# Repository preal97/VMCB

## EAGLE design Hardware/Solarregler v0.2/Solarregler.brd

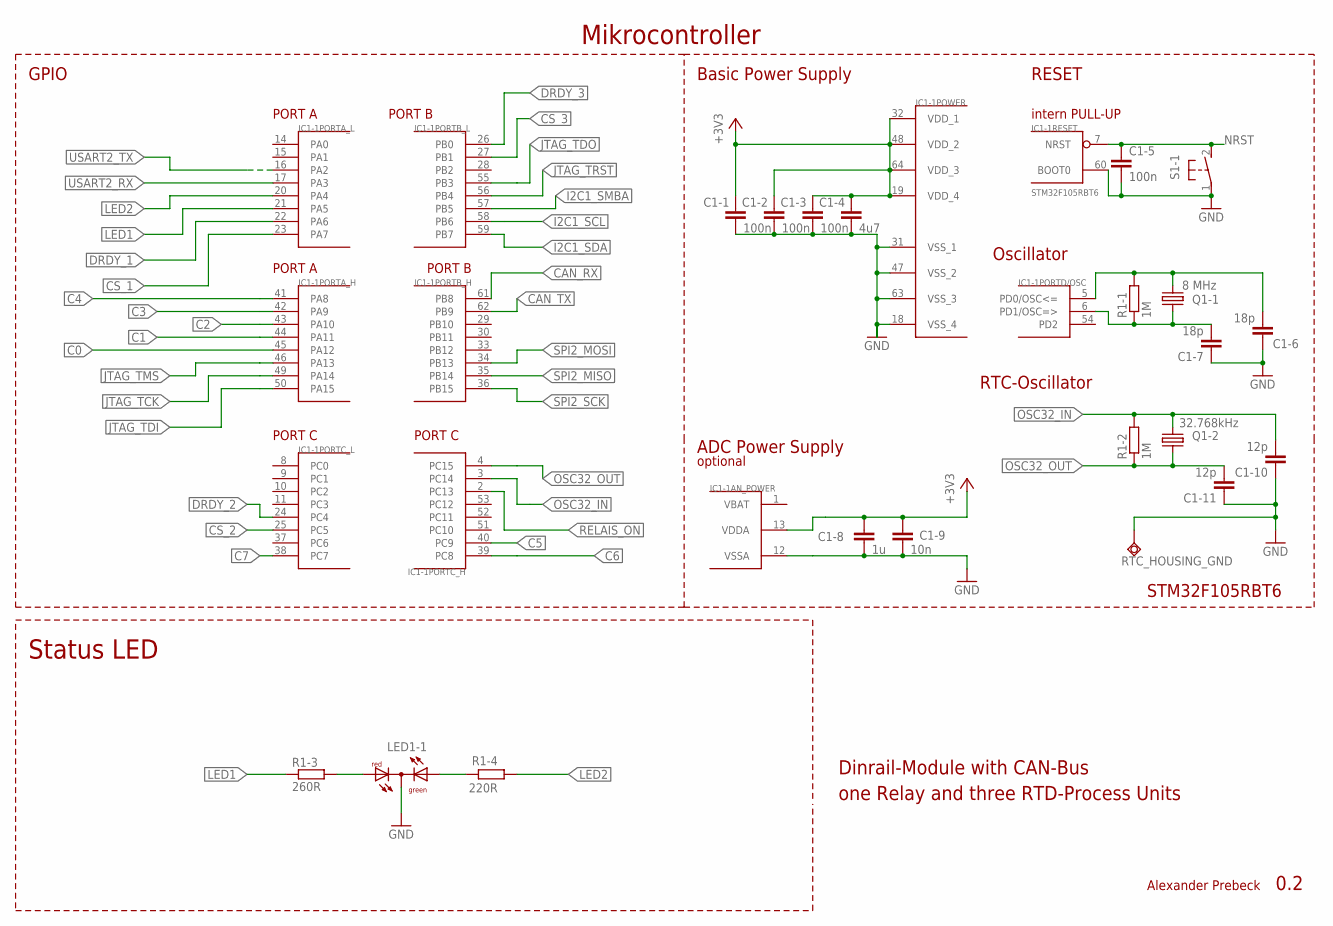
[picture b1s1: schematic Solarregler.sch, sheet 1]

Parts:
C1-1, C1-2, C1-3, C1-5: 100n; C0603; MPN C0805C104K1RAC AUTO
C1-4: 4u7; C1206; MPN GRM21BR61A475KA73L
C1-6, C1-7: 18p; C0603; MPN C0805C270J5GACTU
C1-8: 1u; C0805; MPN GRM21BR71E105KA99L
C1-9: 10n; C0603; MPN MC0805B103K500CT
C1-10, C1-11: 12p; C0603; MPN C0805C270J5GACTU
IC1-1: STM32F105RBT6; TQFP64
LED1-1: DUOLED-RG-C; DUOLED-C-5MM
Q1-1: 8 MHz; SMD_QUARZ_6X3.5MM
Q1-2: 32.768kHz; THROUGH_HOLE_QUARZ_RTC
R1-1, R1-2: 1M; R0603
R1-3: 260R; R0603
R1-4: 220R; R0603
RTC_HOUSING_GND: TPSQTP20SQ; TP20SQ
S1-1: 31-XX; B3F-31XX

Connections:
+3V3: C1-1.1, C1-2.1, C1-3.1, C1-4.1, C1-8.1, C1-9.1, IC1-1.13 (VDDA), IC1-1.19 (VDD_4), IC1-1.32 (VDD_1), IC1-1.48 (VDD_2), IC1-1.64 (VDD_3); also elsewhere on the board
C0: IC1-1.45 (PA12); also elsewhere on the board
C1: IC1-1.44 (PA11); also elsewhere on the board
C2: IC1-1.43 (PA10); also elsewhere on the board
C3: IC1-1.42 (PA9); also elsewhere on the board
C4: IC1-1.41 (PA8); also elsewhere on the board
C5: IC1-1.40 (PC9); also elsewhere on the board
C6: IC1-1.39 (PC8); also elsewhere on the board
C7: IC1-1.38 (PC7); also elsewhere on the board
CAN_RX: IC1-1.61 (PB8); also elsewhere on the board
CAN_TX: IC1-1.62 (PB9); also elsewhere on the board
CS_1: IC1-1.23 (PA7); also elsewhere on the board
CS_2: IC1-1.25 (PC5); also elsewhere on the board
CS_3: IC1-1.27 (PB1); also elsewhere on the board
DRDY_1: IC1-1.22 (PA6); also elsewhere on the board
DRDY_2: IC1-1.24 (PC4); also elsewhere on the board
DRDY_3: IC1-1.26 (PB0); also elsewhere on the board
GND: C1-1.2, C1-2.2, C1-3.2, C1-4.2, C1-5.2, C1-6.1, C1-7.1, C1-8.2, C1-9.2, C1-10.1, C1-11.1, IC1-1.12 (VSSA), IC1-1.18 (VSS_4), IC1-1.31 (VSS_1), IC1-1.47 (VSS_2), IC1-1.60 (BOOT0), IC1-1.63 (VSS_3), LED1-1.C, RTC_HOUSING_GND.TP, S1-1.1; also elsewhere on the board
I2C1_SCL: IC1-1.58 (PB6); also elsewhere on the board
I2C1_SDA: IC1-1.59 (PB7); also elsewhere on the board
I2C1_SMBA: IC1-1.57 (PB5); also elsewhere on the board
JTAG_TCK: IC1-1.49 (PA14); also elsewhere on the board
JTAG_TDI: IC1-1.50 (PA15); also elsewhere on the board
JTAG_TDO: IC1-1.55 (PB3); also elsewhere on the board
JTAG_TMS: IC1-1.46 (PA13); also elsewhere on the board
JTAG_TRST: IC1-1.56 (PB4); also elsewhere on the board
LED1: IC1-1.21 (PA5), R1-3.1
LED2: IC1-1.20 (PA4), R1-4.1
unnamed: LED1-1.AX (AG), R1-4.2
unnamed: LED1-1.AR, R1-3.2
unnamed: C1-7.2, IC1-1.6 (PD1/OSC=>), Q1-1.1, R1-1.1
unnamed: C1-6.2, IC1-1.5 (PD0/OSC<=), Q1-1.2, R1-1.2
NRST: C1-5.1, IC1-1.7 (NRST), S1-1.2 (S); also elsewhere on the board
OSC32_IN: C1-10.2, IC1-1.3 (PC14), Q1-2.P$1 (1), R1-2.2
OSC32_OUT: C1-11.2, IC1-1.4 (PC15), Q1-2.P$2 (2), R1-2.1
RELAIS_ON: IC1-1.2 (PC13); also elsewhere on the board
SPI2_MISO: IC1-1.35 (PB14); also elsewhere on the board
SPI2_MOSI: IC1-1.34 (PB13); also elsewhere on the board
SPI2_SCK: IC1-1.36 (PB15); also elsewhere on the board
USART2_RX: IC1-1.17 (PA3); also elsewhere on the board
USART2_TX: IC1-1.16 (PA2); also elsewhere on the board
VBAT: IC1-1.1 (VBAT)

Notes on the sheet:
Mikrocontroller
Dinrail-Module with CAN-Bus
one Relay and three RTD-Process Units
0.2
Status LED
Alexander Prebeck
intern PULL-UP
RESET
PORT A
PORT B
PORT C
GPIO
Oscillator
ADC Power Supply
Basic Power Supply
STM32F105RBT6
RTC-Oscillator
optional

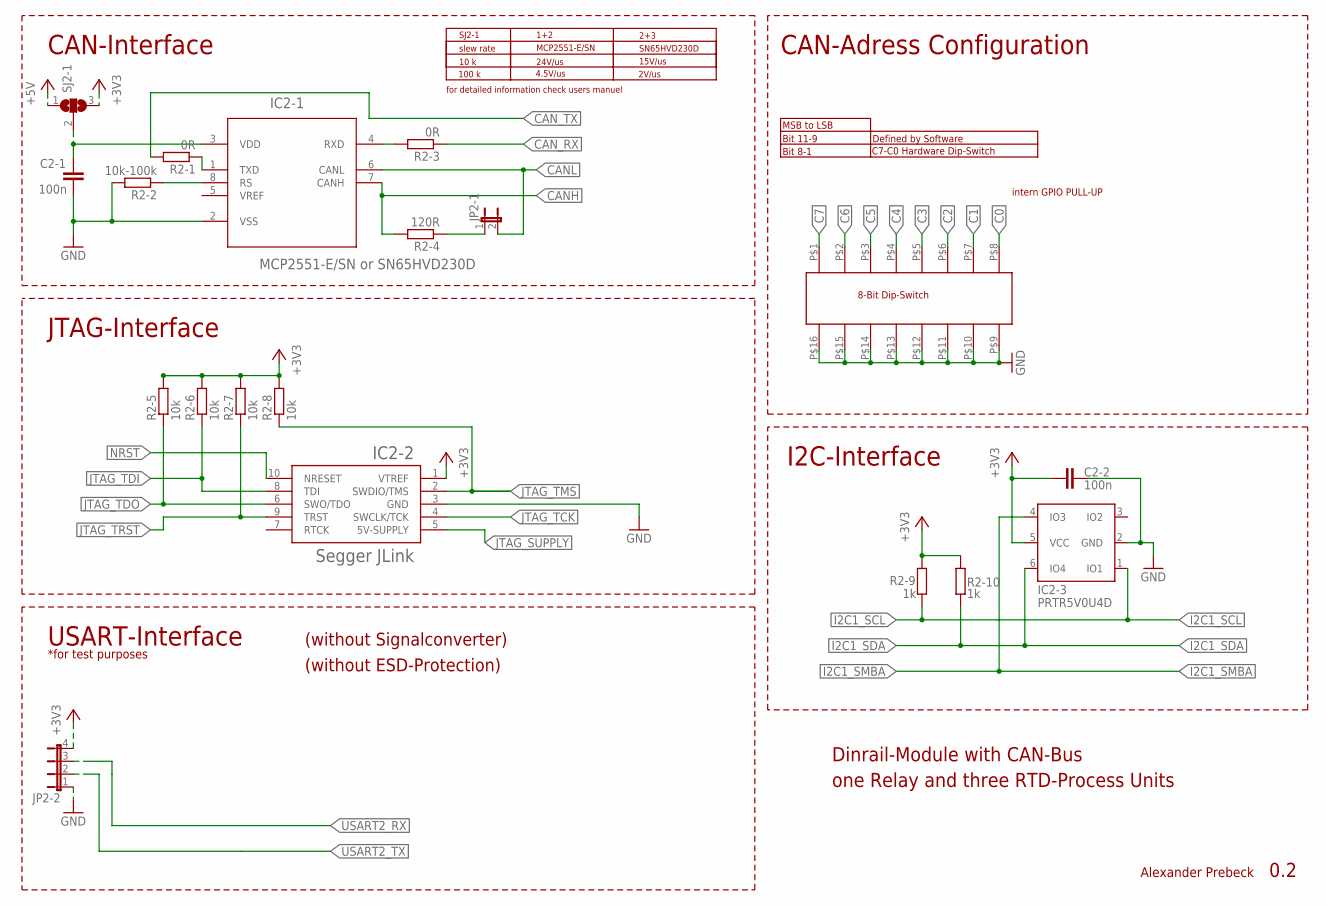
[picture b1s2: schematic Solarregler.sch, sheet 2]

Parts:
C2-1, C2-2: 100n; C0603; MPN C0805C104K1RAC AUTO
DIP21: MULTICOMP
IC2-1: MCP2551-E/SN or SN65HVD230D; SOIC127P600X175-8N
IC2-2: J-LINK-10PIN-HOLES
IC2-3: PRTR5V0U4D; SC74; MPN PRTR5V0U4D,125.
JP2-1: JP1E; JP1
JP2-2: JP4E; JP4
R2-1, R2-3: 0R; R0603
R2-2: 10k-100k; R0603
R2-4: 120R; R0603
R2-5, R2-6, R2-7, R2-8: 10k; R0603
R2-9, R2-10: 1k; R0603
SJ2-1: SJ2W; SJ_2

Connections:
+3V3: C2-2.1, IC2-2.1 (VTREF), IC2-3.5 (VCC), JP2-2.4, R2-5.2, R2-6.2, R2-7.2, R2-8.2, R2-9.2, R2-10.2, SJ2-1.3; also elsewhere on the board
+5V: SJ2-1.1; also elsewhere on the board
C0: DIP21.P$8; also elsewhere on the board
C1: DIP21.P$7; also elsewhere on the board
C2: DIP21.P$6; also elsewhere on the board
C3: DIP21.P$5; also elsewhere on the board
C4: DIP21.P$4; also elsewhere on the board
C5: DIP21.P$3; also elsewhere on the board
C6: DIP21.P$2; also elsewhere on the board
C7: DIP21.P$1 (1); also elsewhere on the board
CANH: IC2-1.7 (CANH), R2-4.2; also elsewhere on the board
CANL: IC2-1.6 (CANL), JP2-1.2; also elsewhere on the board
CAN_RX: R2-3.1; also elsewhere on the board
CAN_TERM2: JP2-1.1, R2-4.1
CAN_TX: R2-1.2; also elsewhere on the board
GND: C2-1.2, C2-2.2, DIP21.P$9, DIP21.P$10, DIP21.P$11, DIP21.P$12, DIP21.P$13, DIP21.P$14, DIP21.P$15, DIP21.P$16, IC2-1.2 (VSS), IC2-2.3 (GND), IC2-3.2 (GND), JP2-2.1, R2-2.2; also elsewhere on the board
I2C1_SCL: IC2-3.1 (IO1), R2-9.1; also elsewhere on the board
I2C1_SDA: IC2-3.6 (IO4), R2-10.1; also elsewhere on the board
I2C1_SMBA: IC2-3.4 (IO3); also elsewhere on the board
JTAG_SUPPLY: IC2-2.5 (5V-SUPPLY); also elsewhere on the board
JTAG_TCK: IC2-2.4 (SWCLK/TCK); also elsewhere on the board
JTAG_TDI: IC2-2.8 (TDI), R2-6.1; also elsewhere on the board
JTAG_TDO: IC2-2.6 (SWO/TDO), R2-5.1; also elsewhere on the board
JTAG_TMS: IC2-2.2 (SWDIO/TMS), R2-8.1; also elsewhere on the board
JTAG_TRST: IC2-2.9 (TRST), R2-7.1; also elsewhere on the board
unnamed: IC2-1.4 (RXD), R2-3.2
unnamed: IC2-1.1 (TXD), R2-1.1
unnamed: IC2-1.8 (RS), R2-2.1
unnamed: C2-1.1, IC2-1.3 (VDD), SJ2-1.2
NRST: IC2-2.10 (NRESET); also elsewhere on the board
USART2_RX: JP2-2.3; also elsewhere on the board
USART2_TX: JP2-2.2; also elsewhere on the board

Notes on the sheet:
CAN-Interface
I2C-Interface
JTAG-Interface
USART-Interface
Dinrail-Module with CAN-Bus
0.2
one Relay and three RTD-Process Units
Alexander Prebeck
*for test purposes
slew rate
MCP2551-E/SN
SN65HVD230D
10 k
100 k
24V/us
4.5V/us
15V/us
2V/us
for detailed information check users manuel
SJ2-1
1+2
2+3
CAN-Adress Configuration
Bit 8-1
Bit 11-9
C7-C0 Hardware Dip-Switch
Defined by Software
MSB to LSB
intern GPIO PULL-UP
8-Bit Dip-Switch
(without Signalconverter)
(without ESD-Protection)

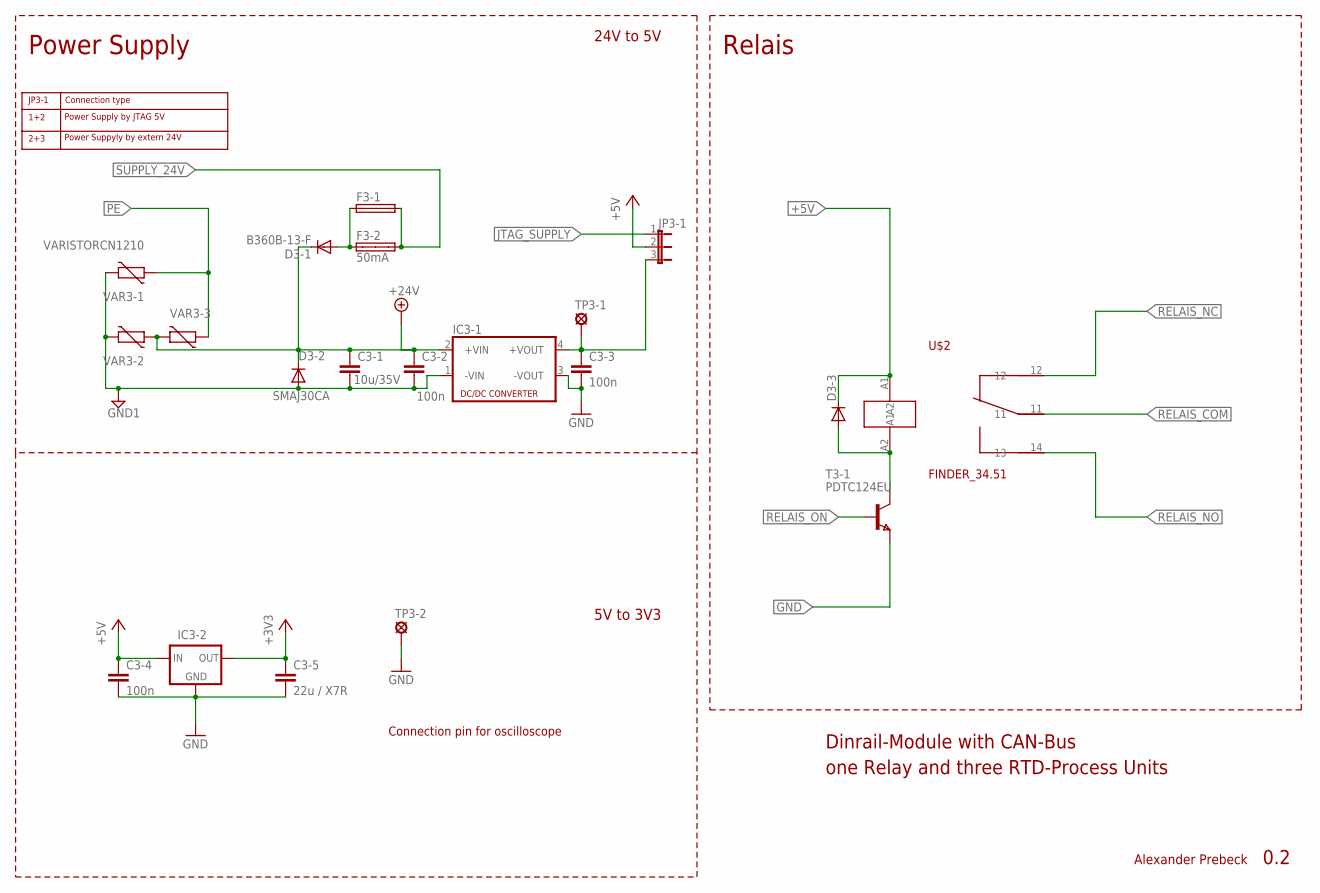
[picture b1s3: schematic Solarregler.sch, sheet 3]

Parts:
C3-1: 10u/35V; C0805; MPN GRM31CC8YA106KA12L
C3-2, C3-3, C3-4: 100n; C0603; MPN C0805C104K1RAC AUTO
C3-5: 22u / X7R; C0805; MPN C0805C104K1RAC AUTO
D3-1: B360B-13-F; SMB; MPN B360B-13-F
D3-2: SMAJ30CA; DO214AA; MPN SMAJ30CA
D3-3: DIODE-SMB; SMB
F3-1: FUSE_1210; 1210
F3-2: 50mA; SHK20Q; MPN 0031.8201
IC3-1: SIM1; 4SIL; MPN IE2405S
IC3-2: MIC5209; SOT223; MPN MIC5209-3.3YS TR
JP3-1: JP2E; JP2
T3-1: PDTC124EU; SOT323
TP3-1, TP3-2: LSP10
U$2: FINDER_34.51; SERIES_34
VAR3-1, VAR3-2, VAR3-3: VARISTORCN1210; CT/CN1210; MPN VC121030H620DP

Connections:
+3V3: C3-5.1, IC3-2.3 (OUT); also elsewhere on the board
+5V: C3-4.1, D3-3.C, IC3-2.1 (IN), JP3-1.2, U$2.A1; also elsewhere on the board
+24V: C3-1.1, C3-2.1, D3-1.C, D3-2.C, IC3-1.2 (+VIN), VAR3-2.2, VAR3-3.2
GND: C3-3.2, C3-4.2, C3-5.2, IC3-1.3 (-VOUT), IC3-2.2 (GND), IC3-2.4 (GND), T3-1.3 (E), TP3-2.MP; also elsewhere on the board
GND1: C3-1.2, C3-2.2, D3-2.A, IC3-1.1 (-VIN), VAR3-1.1, VAR3-2.1; also elsewhere on the board
JTAG_SUPPLY: JP3-1.1; also elsewhere on the board
unnamed: D3-3.A, T3-1.1 (C), U$2.A2
unnamed: C3-3.1, IC3-1.4 (+VOUT), JP3-1.3, TP3-1.MP
unnamed: D3-1.A, F3-1.1, F3-2.1A
PE: VAR3-1.2, VAR3-3.1; also elsewhere on the board
RELAIS_COM: U$2.11; also elsewhere on the board
RELAIS_NC: U$2.12; also elsewhere on the board
RELAIS_NO: U$2.14 (13); also elsewhere on the board
RELAIS_ON: T3-1.2 (B); also elsewhere on the board
SUPPLY_24V: F3-1.2, F3-2.2A; also elsewhere on the board

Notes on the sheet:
Power Supply
Connection pin for oscilloscope
24V to 5V
5V to 3V3
JP3-1
1+2
2+3
Power Supply by JTAG 5V
Power Suppyly by extern 24V
Connection type
Relais
0.2
Dinrail-Module with CAN-Bus
one Relay and three RTD-Process Units
Alexander Prebeck

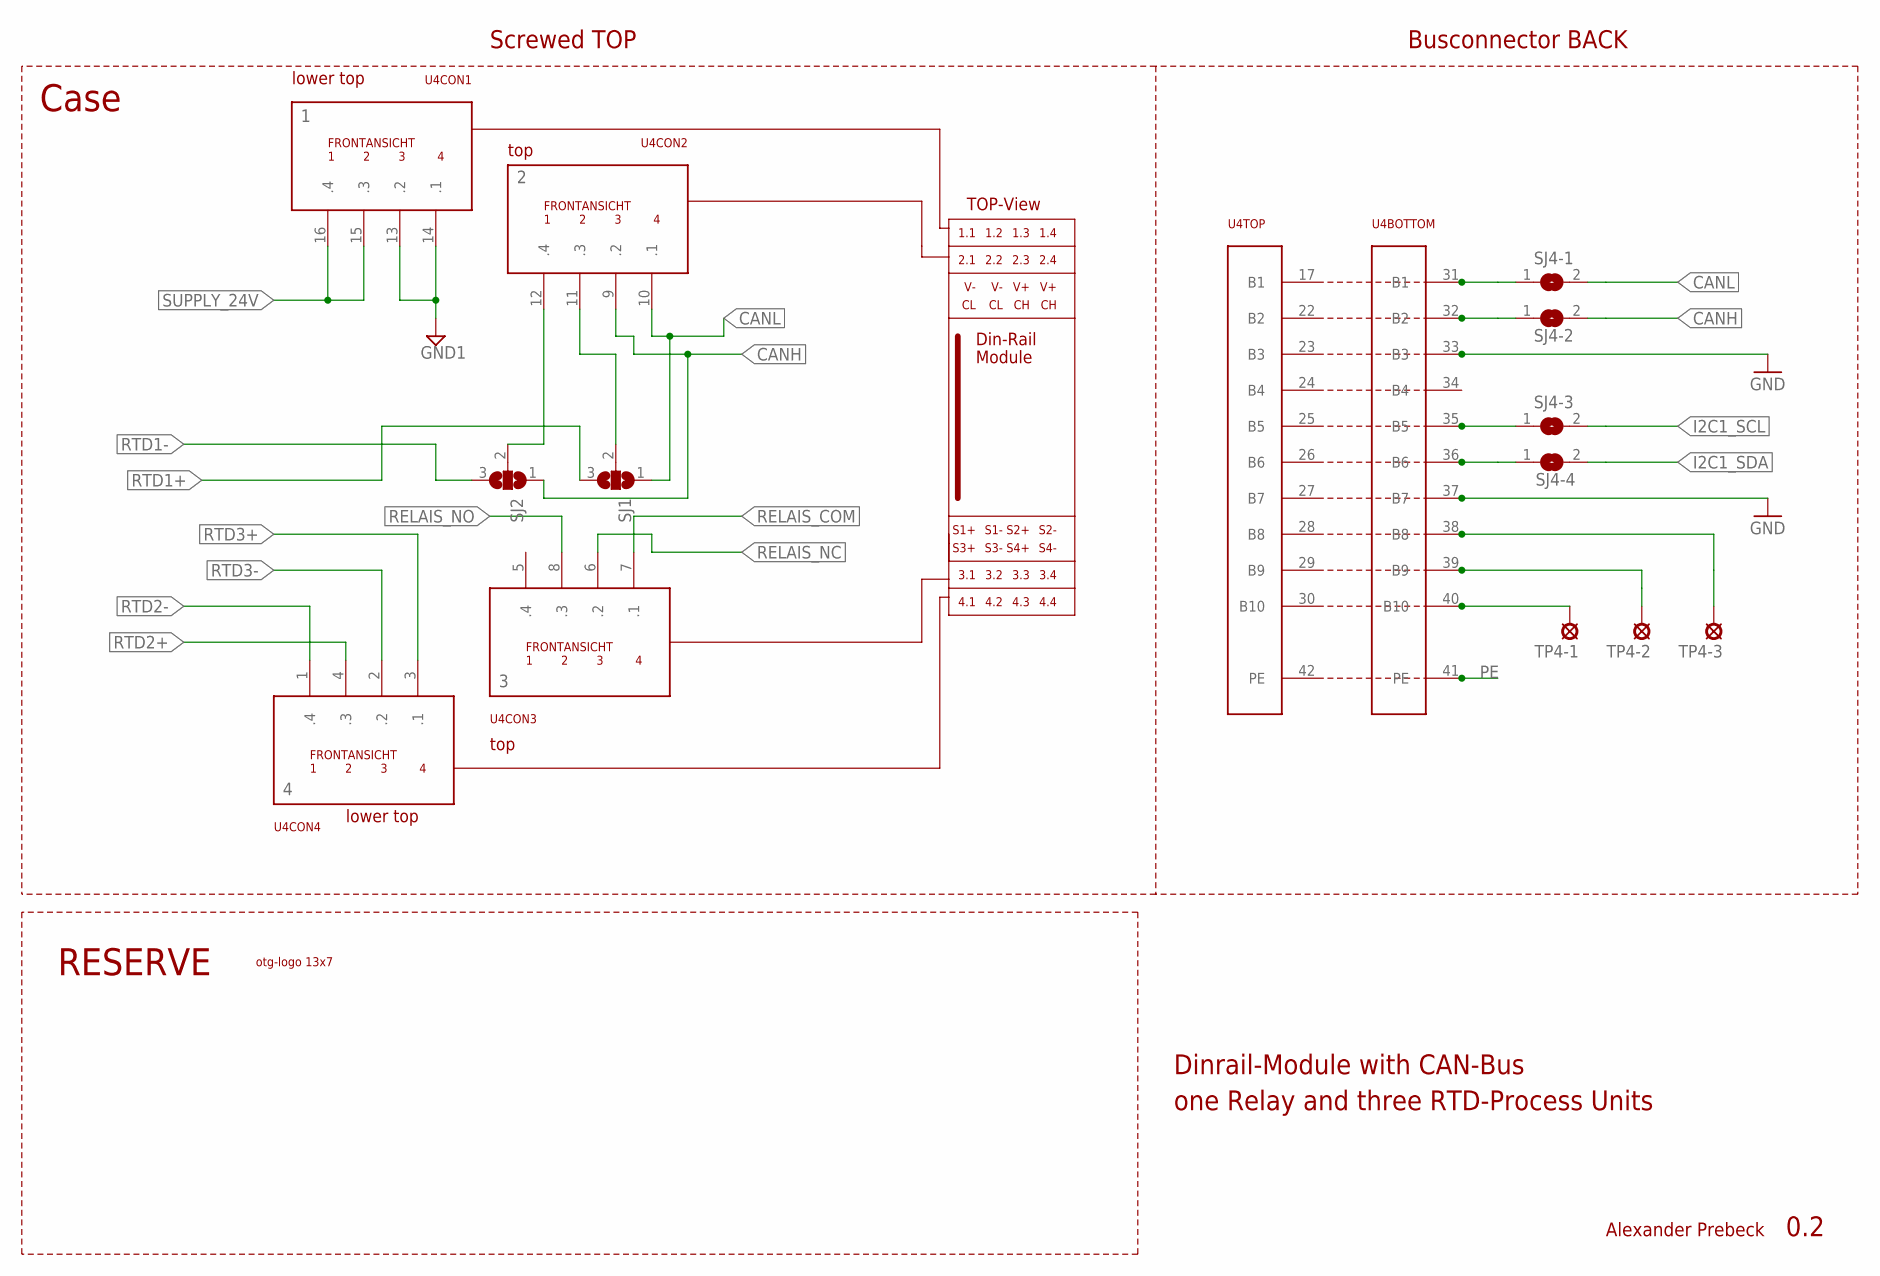
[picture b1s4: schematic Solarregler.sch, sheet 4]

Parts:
SJ1, SJ2: SJ2W; SJ_2
SJ4-1, SJ4-2, SJ4-3, SJ4-4: SJW
TP4-1, TP4-2, TP4-3: LSP10
U4: HUTSCHIENE_DEV; HUTSCHIENE
U$1: OTH-LOGO13X7; OTH-LOGO_SMALL

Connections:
CANH: SJ2.1, SJ4-2.2, U4.9 (.2); also elsewhere on the board
CANL: SJ1.1, SJ4-1.2, U4.10 (.1); also elsewhere on the board
GND: U4.33 (B3), U4.37 (B7); also elsewhere on the board
GND1: U4.13 (.2), U4.14 (.1); also elsewhere on the board
I2C1_SCL: SJ4-3.2; also elsewhere on the board
I2C1_SDA: SJ4-4.2; also elsewhere on the board
unnamed: SJ1.2, U4.11 (.3)
unnamed: SJ2.2, U4.12 (.4)
unnamed: SJ4-1.1, U4.31 (B1)
unnamed: SJ4-2.1, U4.32 (B2)
unnamed: SJ4-3.1, U4.35 (B5)
unnamed: SJ4-4.1, U4.36 (B6)
unnamed: TP4-3.MP, U4.38 (B8)
unnamed: TP4-2.MP, U4.39 (B9)
unnamed: TP4-1.MP, U4.40 (B10)
PE: U4.41 (PE); also elsewhere on the board
RELAIS_COM: U4.7 (.1); also elsewhere on the board
RELAIS_NC: U4.6 (.2); also elsewhere on the board
RELAIS_NO: U4.8 (.3); also elsewhere on the board
RTD1+: SJ1.3; also elsewhere on the board
RTD1-: SJ2.3; also elsewhere on the board
RTD2+: U4.4 (.3); also elsewhere on the board
RTD2-: U4.1 (.4); also elsewhere on the board
RTD3+: U4.3 (.1); also elsewhere on the board
RTD3-: U4.2 (.2); also elsewhere on the board
SUPPLY_24V: U4.15 (.3), U4.16 (.4); also elsewhere on the board

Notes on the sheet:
Case
lower top
top
Screwed TOP
Busconnector BACK
1.1
1.2
1.3
1.4
2.1
2.2
2.3
2.4
TOP-View
Din-Rail
Module
Dinrail-Module with CAN-Bus
0.2
one Relay and three RTD-Process Units
Alexander Prebeck
3.1
3.2
3.3
3.4
4.1
4.2
4.3
4.4
S1-
S1+
S3+
S2-
S2+
S4+
S4-
S3-
RESERVE

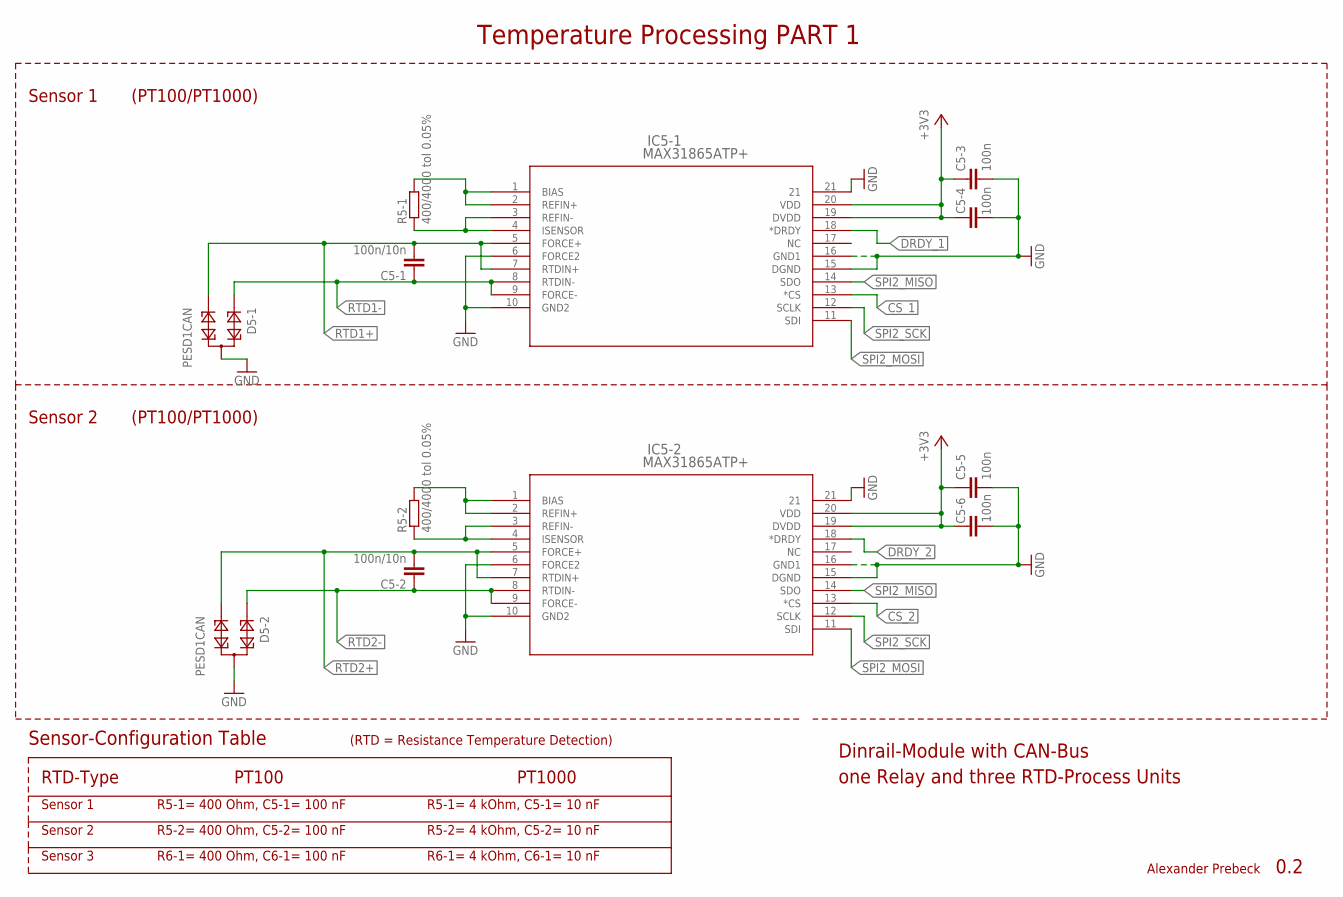
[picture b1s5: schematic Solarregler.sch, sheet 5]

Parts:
C5-1, C5-2: 100n/10n; C0603
C5-3, C5-4, C5-5, C5-6: 100n; C0603
D5-1, D5-2: PESD1CAN; SOT23
IC5-1, IC5-2: MAX31865ATP+; 21-0140L_T2055-5
R5-1, R5-2: 400/4000 tol 0.05%; R0603

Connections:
+3V3: C5-3.1, C5-4.1, C5-5.1, C5-6.1, IC5-1.19 (DVDD), IC5-1.20 (VDD), IC5-2.19 (DVDD), IC5-2.20 (VDD); also elsewhere on the board
CS_1: IC5-1.13 (*CS); also elsewhere on the board
CS_2: IC5-2.13 (*CS); also elsewhere on the board
DRDY_1: IC5-1.18 (*DRDY); also elsewhere on the board
DRDY_2: IC5-2.18 (*DRDY); also elsewhere on the board
GND: C5-3.2, C5-4.2, C5-5.2, C5-6.2, D5-1.3, D5-2.3, IC5-1.6 (FORCE2), IC5-1.10 (GND2), IC5-1.15 (DGND), IC5-1.16 (GND1), IC5-1.21, IC5-2.6 (FORCE2), IC5-2.10 (GND2), IC5-2.15 (DGND), IC5-2.16 (GND1), IC5-2.21; also elsewhere on the board
unnamed: IC5-1.1 (BIAS), IC5-1.2 (REFIN+), R5-1.2
unnamed: IC5-1.3 (REFIN-), IC5-1.4 (ISENSOR), R5-1.1
unnamed: IC5-2.1 (BIAS), IC5-2.2 (REFIN+), R5-2.2
unnamed: IC5-2.3 (REFIN-), IC5-2.4 (ISENSOR), R5-2.1
RTD1+: C5-1.2, D5-1.2, IC5-1.5 (FORCE+), IC5-1.7 (RTDIN+); also elsewhere on the board
RTD1-: C5-1.1, D5-1.1, IC5-1.8 (RTDIN-), IC5-1.9 (FORCE-); also elsewhere on the board
RTD2+: C5-2.2, D5-2.2, IC5-2.5 (FORCE+), IC5-2.7 (RTDIN+); also elsewhere on the board
RTD2-: C5-2.1, D5-2.1, IC5-2.8 (RTDIN-), IC5-2.9 (FORCE-); also elsewhere on the board
SPI2_MISO: IC5-1.14 (SDO), IC5-2.14 (SDO); also elsewhere on the board
SPI2_MOSI: IC5-1.11 (SDI), IC5-2.11 (SDI); also elsewhere on the board
SPI2_SCK: IC5-1.12 (SCLK), IC5-2.12 (SCLK); also elsewhere on the board

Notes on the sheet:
Temperature Processing PART 1
Sensor 1
Sensor 2
Dinrail-Module with CAN-Bus
0.2
one Relay and three RTD-Process Units
Alexander Prebeck
Sensor-Configuration Table
(PT100/PT1000)
(RTD = Resistance Temperature Detection)
PT100
PT1000
Sensor 3
R5-1= 400 Ohm, C5-1= 100 nF
R5-2= 400 Ohm, C5-2= 100 nF
R6-1= 400 Ohm, C6-1= 100 nF
R5-1= 4 kOhm, C5-1= 10 nF
R5-2= 4 kOhm, C5-2= 10 nF
R6-1= 4 kOhm, C6-1= 10 nF
RTD-Type

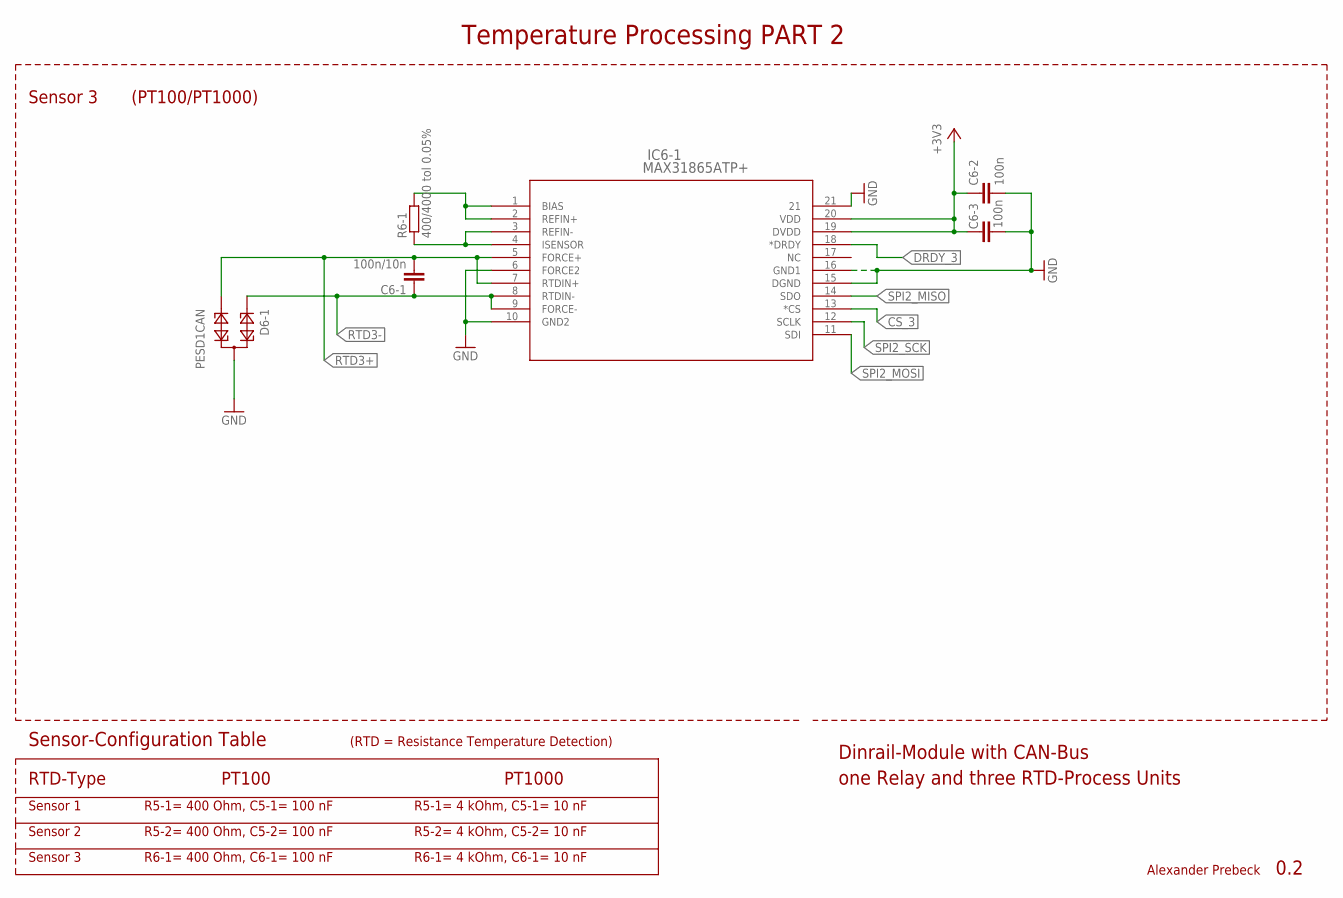
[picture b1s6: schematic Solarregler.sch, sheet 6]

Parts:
C6-1: 100n/10n; C0603
C6-2, C6-3: 100n; C0603
D6-1: PESD1CAN; SOT23
IC6-1: MAX31865ATP+; 21-0140L_T2055-5
R6-1: 400/4000 tol 0.05%; R0603

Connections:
+3V3: C6-2.1, C6-3.1, IC6-1.19 (DVDD), IC6-1.20 (VDD); also elsewhere on the board
CS_3: IC6-1.13 (*CS); also elsewhere on the board
DRDY_3: IC6-1.18 (*DRDY); also elsewhere on the board
GND: C6-2.2, C6-3.2, D6-1.3, IC6-1.6 (FORCE2), IC6-1.10 (GND2), IC6-1.15 (DGND), IC6-1.16 (GND1), IC6-1.21; also elsewhere on the board
unnamed: IC6-1.1 (BIAS), IC6-1.2 (REFIN+), R6-1.2
unnamed: IC6-1.3 (REFIN-), IC6-1.4 (ISENSOR), R6-1.1
RTD3+: C6-1.2, D6-1.2, IC6-1.5 (FORCE+), IC6-1.7 (RTDIN+); also elsewhere on the board
RTD3-: C6-1.1, D6-1.1, IC6-1.8 (RTDIN-), IC6-1.9 (FORCE-); also elsewhere on the board
SPI2_MISO: IC6-1.14 (SDO); also elsewhere on the board
SPI2_MOSI: IC6-1.11 (SDI); also elsewhere on the board
SPI2_SCK: IC6-1.12 (SCLK); also elsewhere on the board

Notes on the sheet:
Dinrail-Module with CAN-Bus
0.2
one Relay and three RTD-Process Units
Alexander Prebeck
Temperature Processing PART 2
Sensor 3
(PT100/PT1000)
Sensor-Configuration Table
Sensor 1
PT100
PT1000
Sensor 2
R5-1= 400 Ohm, C5-1= 100 nF
R5-2= 400 Ohm, C5-2= 100 nF
R6-1= 400 Ohm, C6-1= 100 nF
R5-1= 4 kOhm, C5-1= 10 nF
R5-2= 4 kOhm, C5-2= 10 nF
R6-1= 4 kOhm, C6-1= 10 nF
RTD-Type
(RTD = Resistance Temperature Detection)

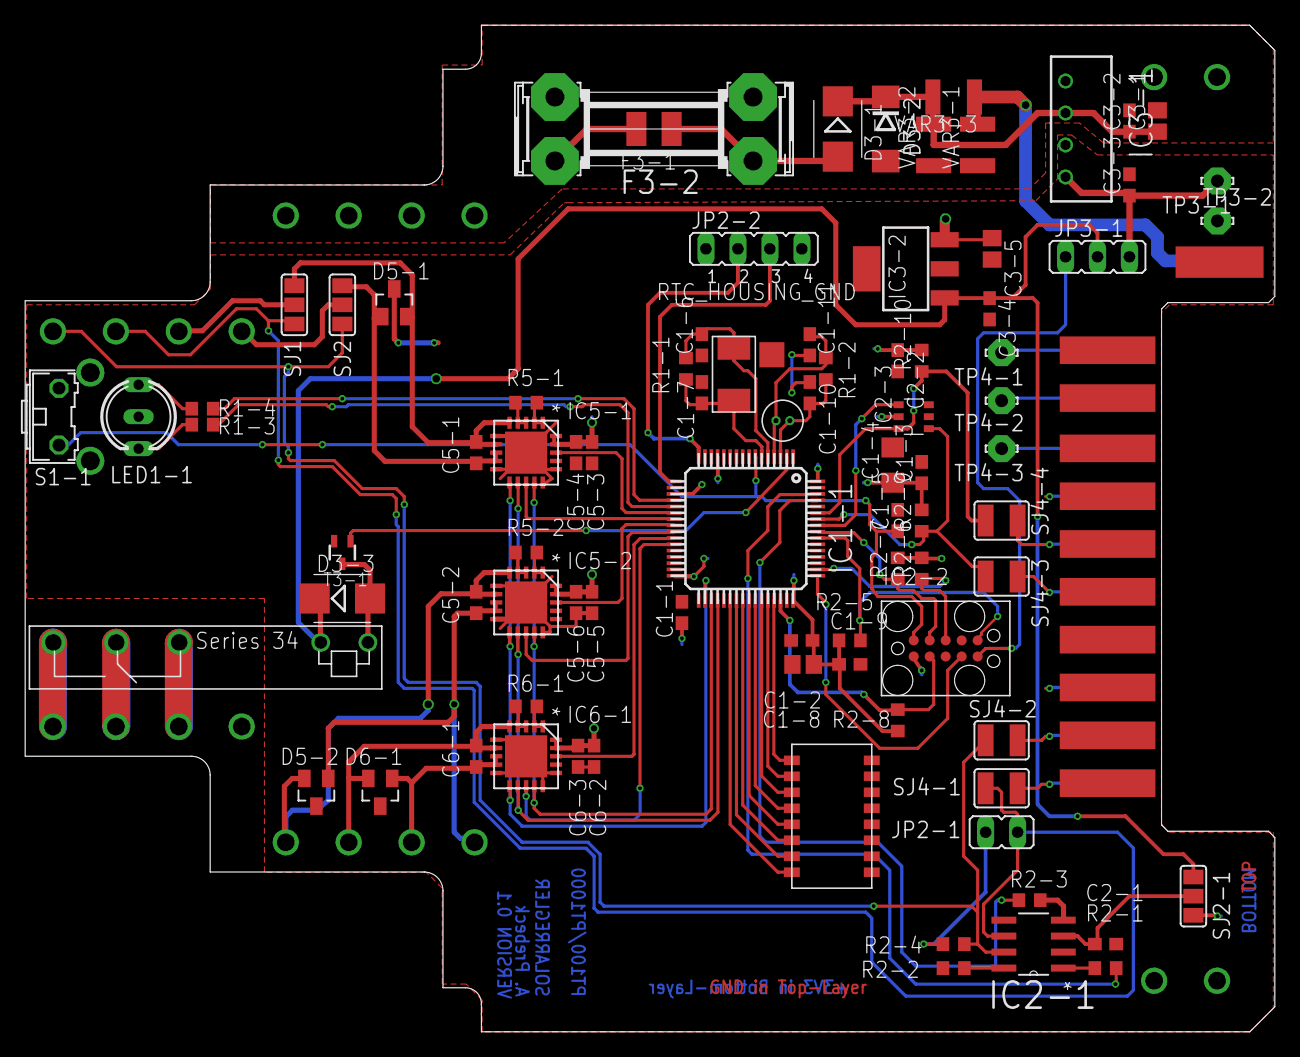
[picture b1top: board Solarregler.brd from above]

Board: 2 copper layers, 99.3 x 80.0 mm, 89 parts (0 on the bottom side), 81 nets.

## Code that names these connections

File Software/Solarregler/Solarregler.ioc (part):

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Mcu.Name=STM32F103R(8-B)Tx
Mcu.Package=LQFP64
Mcu.UserName=STM32F103RBTx
PA10.GPIOParameters=GPIO_PuPd,GPIO_Label
PA10.GPIO_Label=C2
PA10.GPIO_PuPd=GPIO_PULLUP
PA10.Signal=GPIO_Input
PA11.GPIOParameters=GPIO_PuPd,GPIO_Label
PA11.GPIO_Label=C1
PA11.GPIO_PuPd=GPIO_PULLUP
PA11.Signal=GPIO_Input
PA12.GPIOParameters=GPIO_PuPd,GPIO_Label
PA12.GPIO_Label=C0
PA12.GPIO_PuPd=GPIO_PULLUP
PA12.Signal=GPIO_Input
PA13.GPIOParameters=GPIO_Label
PA13.GPIO_Label=TMS
PA13.Mode=JTAG_5_pins
PA13.Signal=SYS_JTMS-SWDIO
PA14.GPIOParameters=GPIO_Label
PA14.GPIO_Label=TCK
PA14.Mode=JTAG_5_pins
PA14.Signal=SYS_JTCK-SWCLK
PA15.Mode=JTAG_5_pins
PA15.Signal=SYS_JTDI
PA2.GPIOParameters=GPIO_Speed,GPIO_PuPd,GPIO_Label,GPIO_Mode
PA2.GPIO_Label=USART_TX
PA2.GPIO_Mode=GPIO_MODE_AF_PP
PA2.GPIO_PuPd=GPIO_NOPULL
PA2.GPIO_Speed=GPIO_SPEED_FREQ_HIGH
PA2.Mode=Asynchronous
PA2.Signal=USART2_TX
PA3.GPIOParameters=GPIO_Speed,GPIO_PuPd,GPIO_Label,GPIO_Mode
PA3.GPIO_Label=USART_RX
PA3.GPIO_Mode=GPIO_MODE_AF_PP
PA3.GPIO_PuPd=GPIO_NOPULL
PA3.GPIO_Speed=GPIO_SPEED_FREQ_LOW
PA3.Mode=Asynchronous
PA3.Signal=USART2_RX
PA4.GPIOParameters=GPIO_Label
PA4.GPIO_Label=LD2
PA4.Signal=GPIO_Output
PA5.GPIOParameters=GPIO_Speed,GPIO_PuPd,GPIO_Label,GPIO_ModeDefaultOutputPP
PA5.GPIO_Label=LD1
PA5.GPIO_ModeDefaultOutputPP=GPIO_MODE_OUTPUT_PP
PA5.GPIO_PuPd=GPIO_NOPULL
PA5.GPIO_Speed=GPIO_SPEED_FREQ_LOW
PA5.Signal=GPIO_Output
PA6.GPIOParameters=GPIO_Label
PA6.GPIO_Label=DRDY_1
PA6.Signal=GPIO_Input
PA7.GPIOParameters=GPIO_Label
PA7.GPIO_Label=CS_1
PA7.Signal=GPIO_Output
PA8.GPIOParameters=GPIO_PuPd,GPIO_Label
PA8.GPIO_Label=C4
PA8.GPIO_PuPd=GPIO_PULLUP
PA8.Signal=GPIO_Input
PA9.GPIOParameters=GPIO_PuPd,GPIO_Label
PA9.GPIO_Label=C3
PA9.GPIO_PuPd=GPIO_PULLUP
PA9.Signal=GPIO_Input
PB0.GPIOParameters=GPIO_Label
PB0.GPIO_Label=DRDY_3
PB0.Signal=GPIO_Input
PB1.GPIOParameters=GPIO_Label
PB1.GPIO_Label=CS_3
PB1.Signal=GPIO_Output
PB11.Signal=GPIO_Input
PB12.Signal=GPIO_Output
PB13.Mode=Full_Duplex_Master
PB13.Signal=SPI2_SCK
PB14.Mode=Full_Duplex_Master
PB14.Signal=SPI2_MISO
PB15.Mode=Full_Duplex_Master
PB15.Signal=SPI2_MOSI
PB3.GPIOParameters=GPIO_Label
PB3.GPIO_Label=SWO
PB3.Mode=JTAG_5_pins
PB3.Signal=SYS_JTDO-TRACESWO
PB4.Mode=JTAG_5_pins
PB4.Signal=SYS_NJTRST
PB5.Mode=SMBus-Alert-mode
PB5.Signal=I2C1_SMBA
PB6.Mode=SMBus-Alert-mode
PB6.Signal=I2C1_SCL
PB7.Mode=SMBus-Alert-mode
PB7.Signal=I2C1_SDA
PB8.Mode=Master
PB8.Signal=CAN_RX
PB9.Mode=Master
PB9.Signal=CAN_TX
PC13-TAMPER-RTC.GPIOParameters=GPIO_PuPd,GPIO_Label
PC13-TAMPER-RTC.GPIO_Label=B1 [Blue PushButton]
PC13-TAMPER-RTC.GPIO_PuPd=GPIO_NOPULL
PC13-TAMPER-RTC.Signal=GPXTI13
PC14-OSC32_IN.Mode=LSE-External-Oscillator
PC14-OSC32_IN.Signal=RCC_OSC32_IN
PC15-OSC32_OUT.Mode=LSE-External-Oscillator
PC15-OSC32_OUT.Signal=RCC_OSC32_OUT
PC4.GPIOParameters=GPIO_Label
PC4.GPIO_Label=DRDY_2
PC4.Signal=GPIO_Input
PC5.GPIOParameters=GPIO_Label
PC5.GPIO_Label=CS_2
PC5.Signal=GPIO_Output
PC7.GPIOParameters=GPIO_PuPd,GPIO_Label
PC7.GPIO_Label=C7
PC7.GPIO_PuPd=GPIO_PULLUP
PC7.Signal=GPIO_Input
PC8.GPIOParameters=GPIO_PuPd,GPIO_Label
PC8.GPIO_Label=C6
PC8.GPIO_PuPd=GPIO_PULLUP
PC8.Signal=GPIO_Input
PC9.GPIOParameters=GPIO_PuPd,GPIO_Label
PC9.GPIO_Label=C5
PC9.GPIO_PuPd=GPIO_PULLUP
PC9.Signal=GPIO_Input
PD0-OSC_IN.Mode=HSE-External-Clock-Source
PD0-OSC_IN.Signal=RCC_OSC_IN
PD1-OSC_OUT.Mode=HSE-External-Clock-Source
PD1-OSC_OUT.Signal=RCC_OSC_OUT
RCC.HSEDivPLL=RCC_HSE_PREDIV_DIV2
RCC.SYSCLKFreq_VALUE=36000000
RCC.SYSCLKSource=RCC_SYSCLKSOURCE_PLLCLK
board=NUCLEO-F103RB
boardIOC=true

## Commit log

2018-12-05 Aktuelle Version Firmware
2018-12-06 2 Sensoren Implementiert
2018-12-06 Can implementiert
2018-12-09 Änderungen von UNI auf GIT
2018-12-09 CAN Filter implementiert + Fault erkennung der Sensoren
2018-12-10 Layout update nach Gespräch mit ME
2018-12-11 can interrupt reenable funktion
2018-12-14 CAN funktioniert, canoe angebunden
2018-12-17 MAX MIN und Regler Aktiv implementiert
2018-12-21 RTC, Can und mehr
2018-12-24 Port to STM32F105RBT6
2019-01-18 Serializer, ON-Time, Resistance Correction added
